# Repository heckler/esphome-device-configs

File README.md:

# ESPHome Device Configs

CAH, 2019-03-26 Configuration definitions for local ESPHome devices.

For information on removing secrets from the repository, see this link: <https://github.com/heckler/home-assistant-config/blob/master/secrets_cleanup.md>

## Device-specific configurations

- [ESP32 Camera modules](docs/esp32cam.md)
- [Flashing Sonoff Basic devices with ESPHome](docs/flashing_sonoff_basic.md)
- [Flashing Sonoff Basic R4 (Magic Switch) devices with ESPHome](docs/flashing_sonoff_basic_r4_magic.md)
- [Flashing Sonoff B1 LED bulbs with ESPHome](docs/flashing_sonoff_b1.md)
- [Configuration instructions for the WLED modules](docs/wled_modules.md)

------------------------------------------------------------------------------------------------

## Initial configuration

### Environment setup

- Getting started guide: [ESPHome Getting Started](https://esphome.io/guides/getting_started_command_line.html)
- WSL: ESPHome should already be configured via the wsl_provision bootstrap script

### DevContainers on VSCode

1. Install the VS Code DevContainers extension.
2. Open this folder in VS Code and run: `Dev Containers: Reopen in Container`.
3. Wait for the initial container build to complete. The container installs `esphome==2026.9.1` automatically.
4. Verify the install inside the container:

### DevContainers commandline on the shell

1. Install the DevContainers CLI: `npm install -g @devcontainers/cli`
2. Build and start the container: `devcontainer up --workspace-folder .`
3. Open a shell inside it: `devcontainer exec --workspace-folder . bash`

### Basic operation

```bash
esphome version
```

Start the dashboard from this repository root:

```bash
esphome dashboard .
```

Notes for USB serial flashing from DevContainer:

1. The DevContainer config binds `/dev` and uses `--privileged`, so serial devices (for example `/dev/ttyUSB0`) are available in the container.
2. Ensure your host user has serial permissions (typically membership in the `dialout` group on Linux).
3. Replug USB devices after opening the container if a serial device is not visible.

To update ESPHome:

```bash
pip3 install --upgrade esphome
pip3 install --upgrade virtualenv
```

To install a specific version:

```bash
pip3 uninstall esphome
pip3 install -Iv esphome==2026.6.2
```

The pip commands above are for local (non-DevContainer) installations.

### Updating ESPHome in the DevContainer

When a new ESPHome release is available, update the pinned version in the DevContainer config.

1. Edit the pinned version in `.devcontainer/devcontainer.json` by changing `postCreateCommand` from `esphome==...` to the new release.
2. In VS Code, run `Dev Containers: Rebuild Container`.
3. Confirm the new version:

```bash
esphome version
```

4. Run a quick config validation from the repository root:

```bash
esphome config balcony_sensors.yaml
```

### Creating a new device config (using the wizard)

`esphome hello-world.yaml wizard`

### Building and deploying

`esphome hello-world.yaml run`

### ESPHome dashboard

There is a simple dashboard webserver in ESPHome.  From the folder where the device configs are stored, execute the following command:

`esphome . dashboard`

Then, navigate to the following address: [http://localhost:6052/](http://localhost:6052/)

### Changing the name of a device via OTA

<https://esphome.io/components/esphome.html#changing-esphome-node-name>

1. Change the name of the device on the yaml
2. Use the `use_address` WiFi option to point to the old mDNS name
3. Upload the config, will rename the device, using the old name for OTA
4. Remove `use_address` and upload again (to confirm it finds the new name)

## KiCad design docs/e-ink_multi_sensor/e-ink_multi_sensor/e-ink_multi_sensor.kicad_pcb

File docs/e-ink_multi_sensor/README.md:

# Multi-sensor board with e-ink display

CAH 2026-09-19

## Overview

This is an ESP32-based device with an e-ink display (WeAct 4.2" 3-color) and a number of sensors.  It will read indoor and outdoor temperatures as well as CO2, barometric pressure and relative humidity. The main components are:

- ESP32: YD-ESP32-S3 / ESP32-S3-WROOM-1 Dev N16R8 (44-pin)
- WeAct 4.2" 400x300, 3-color e-ink display (white, black and red)
- BME280 sensor (Barometric pressure, temperature and relative humidity - to be placed outdoors)
- SCD41 (CO2, temperature and relative humidity - to be placed indoors)
- HC-SR501 PIR sensor (for updating the e-ink panel only when there's recent movement)
- WS2812b status LED (1-5 LEDs on a strip, to be defined)
- 2 capacitive switches for input

## Supplier links and price (2026)

| Device     |  Price | Link                                                |
| ---------- | -----: | --------------------------------------------------- |
| ESP32-S3   |  $5.47 | <https://aliexpress.com/item/1005009045226863.html> |
| WeAct 4.2" | $12.44 | <https://aliexpress.com/item/1005008461198386.html> |
| BME280     |  $7.74 | <https://aliexpress.com/item/1005010471387051.html> |
| SCD41      | $12.81 | <https://aliexpress.com/item/1005009392057489.html> |
| HC-SR501   |  $1.29 | <https://aliexpress.com/item/1005006438490597.html> |

## GPIO allocation

|   GPIO | Function       | Device             | Notes                    |
| -----: | -------------- | ------------------ | ------------------------ |
|  GPIO4 | I2C SDA        | BME280 + SCD41     | Good general-purpose pin |
|  GPIO5 | I2C SCL        | BME280 + SCD41     | Good general-purpose pin |
|  GPIO6 | SPI CLK / SCL  | WeAct 4.2" e-paper | E-paper SPI              |
|  GPIO7 | SPI MOSI / SDA | WeAct 4.2" e-paper | E-paper SPI              |
|  GPIO8 | CS             | WeAct 4.2" e-paper | Chip select              |
|  GPIO9 | DC             | WeAct 4.2" e-paper | Data/command             |
| GPIO10 | RST            | WeAct 4.2" e-paper | Display reset            |
| GPIO11 | BUSY           | WeAct 4.2" e-paper | Display busy input       |
| GPIO12 | PIR OUT        | HC-SR501           | Digital input            |
| GPIO13 | DATA           | WS2812B            | Drives 1-5 LEDs          |
| GPIO14 | Switch 1       | Pushbutton/switch  | Digital input            |
| GPIO15 | Switch 2       | Pushbutton/switch  | Digital input            |
| GPIO16 | -              | Spare              | Keep available           |
| GPIO17 | -              | Spare              | Keep available           |
| GPIO18 | -              | Spare              | Keep available           |
| GPIO21 | -              | Spare              | Keep available           |

## Reserved GPIOs

|           GPIO | Reason                                                 |
| -------------: | ------------------------------------------------------ |
| -        GPIO0 | Boot/strapping                                       - |
|          GPIO3 | Strapping                                              |
| -    GPIO19/20 | Native USB D-/D+                                       |
|   GPIO35/36/37 | N16R8 octal PSRAM                                      |
|      GPIO43/44 | USB-UART / UART0                                       |
|         GPIO45 | Strapping                                              |
|         GPIO46 | Strapping                                              |
|         GPIO48 | On-board RGB LED / special-purpose pin                 |
|      GPIO39-42 | JTAG pins; usable, but better retained for debugging   |

## ESPHome configuration

### ESP32 S3 board

```yaml
esp32:
  board: esp32-s3-devkitc-1
  framework:
    type: esp-idf
psram:
  mode: octal
  speed: 80MHz
```

### WeAct 4.2" 3-color e-ink panel

```yaml
spi:
  clk_pin: GPIO6
  mosi_pin: GPIO7

display:
  - platform: epaper_spi
    model: WeAct-4.2in-3c
    cs_pin: GPIO8
    dc_pin: GPIO9
    reset_pin: GPIO10
    busy_pin: GPIO11
```

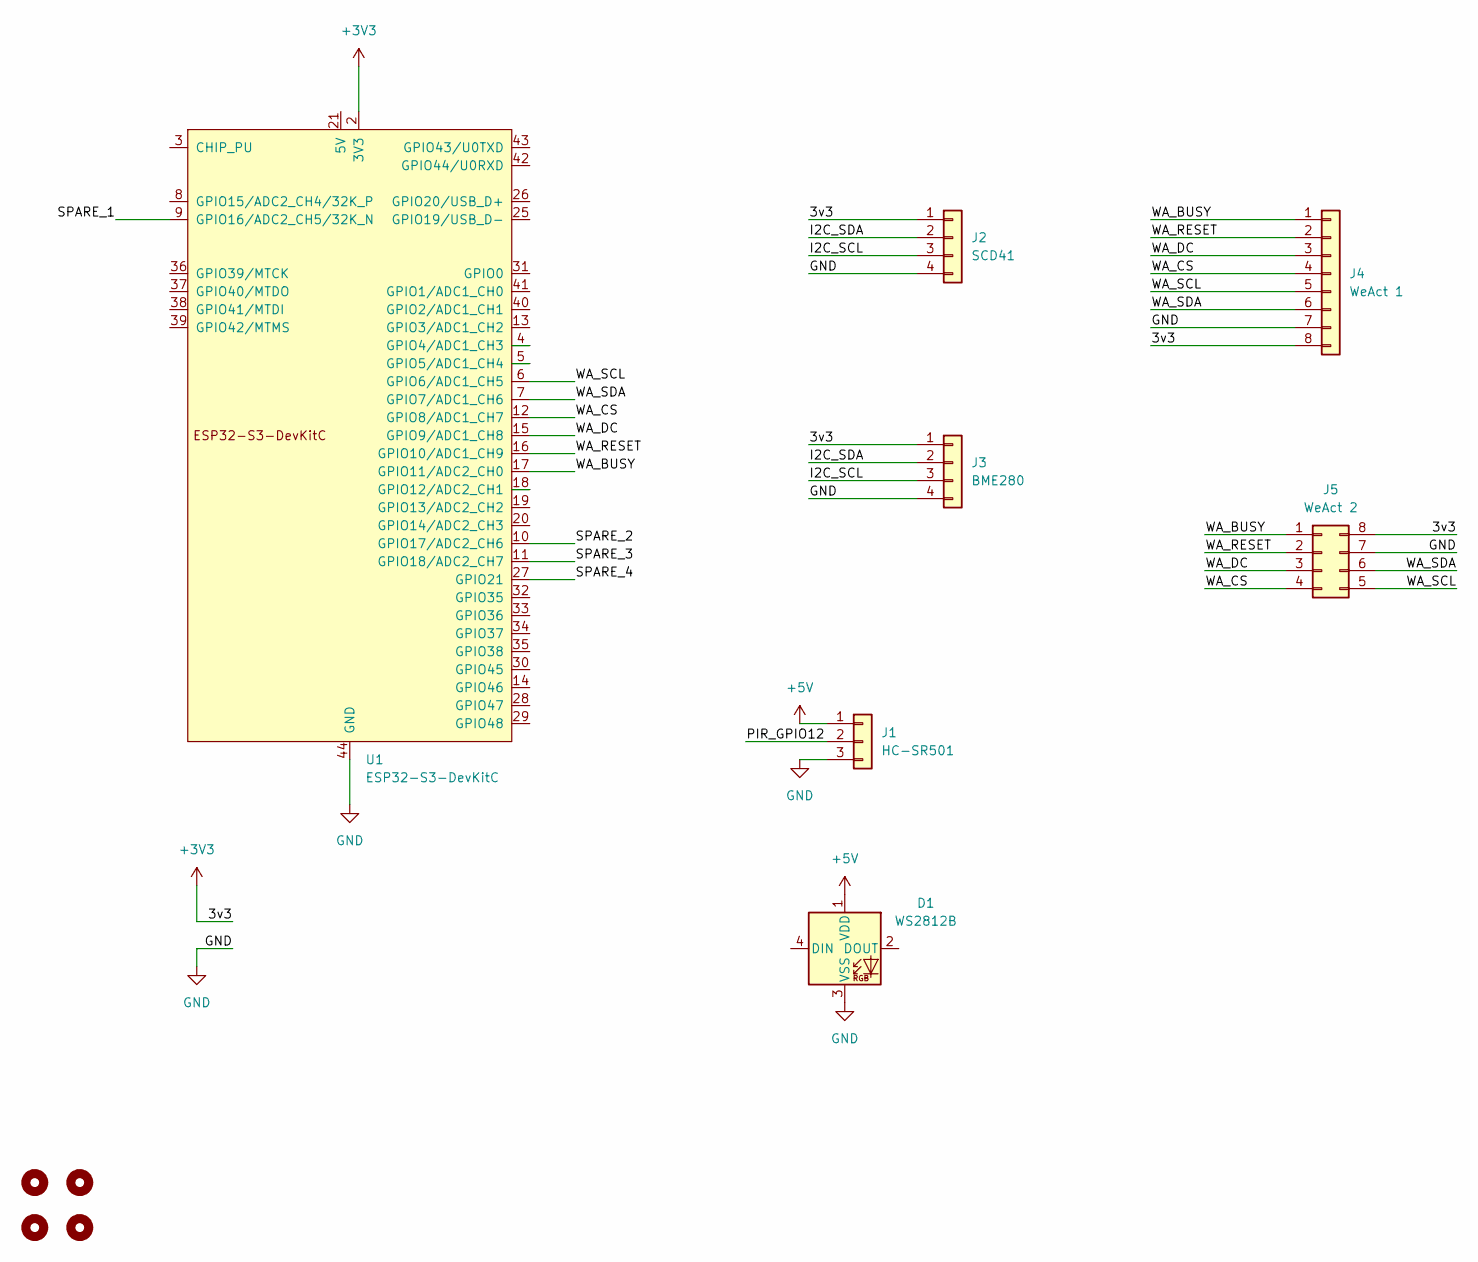
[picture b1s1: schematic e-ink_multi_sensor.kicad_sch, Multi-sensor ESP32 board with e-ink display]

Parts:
D1: WS2812B; LED_WS2812B_PLCC4_5.0x5.0mm_P3.2mm
H1, H2, H3, H4: MountingHole; MountingHole_3mm_Pad
J1: HC-SR501; JST_EH_B3B-EH-A_1x03_P2.50mm_Vertical
J2: SCD41; NS-Tech_Grove_1x04_P2mm_Vertical
J3: BME280; NS-Tech_Grove_1x04_P2mm_Vertical
J4: WeAct 1; JST_PH_B8B-PH-K_1x08_P2.00mm_Vertical
J5: WeAct 2; Hirose_DF11-8DP-2DSA_2x04_P2.00mm_Vertical
U1: ESP32-S3-DevKitC

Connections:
+3V3: J2.1, J3.1, J4.8, J5.8, U1.1 (3V3), U1.2 (3V3)
+5V: D1.1 (VDD), J1.1
/I2C_SCL: J2.3, J3.3
/I2C_SDA: J2.2, J3.2
/PIR_GPIO12: J1.2
/SPARE_1: U1.9 (GPIO16/ADC2_CH5/32K_N)
/SPARE_2: U1.10 (GPIO17/ADC2_CH6)
/SPARE_3: U1.11 (GPIO18/ADC2_CH7)
/SPARE_4: U1.27 (GPIO21)
/WA_BUSY: J4.1, J5.1, U1.17 (GPIO11/ADC2_CH0)
/WA_CS: J4.4, J5.4, U1.12 (GPIO8/ADC1_CH7)
/WA_DC: J4.3, J5.3, U1.15 (GPIO9/ADC1_CH8)
/WA_RESET: J4.2, J5.2, U1.16 (GPIO10/ADC1_CH9)
/WA_SCL: J4.5, J5.5, U1.6 (GPIO6/ADC1_CH5)
/WA_SDA: J4.6, J5.6, U1.7 (GPIO7/ADC1_CH6)
GND: D1.3 (VSS), J1.3, J2.4, J3.4, J4.7, J5.7, U1.22 (GND), U1.23 (GND), U1.24 (GND), U1.44 (GND)

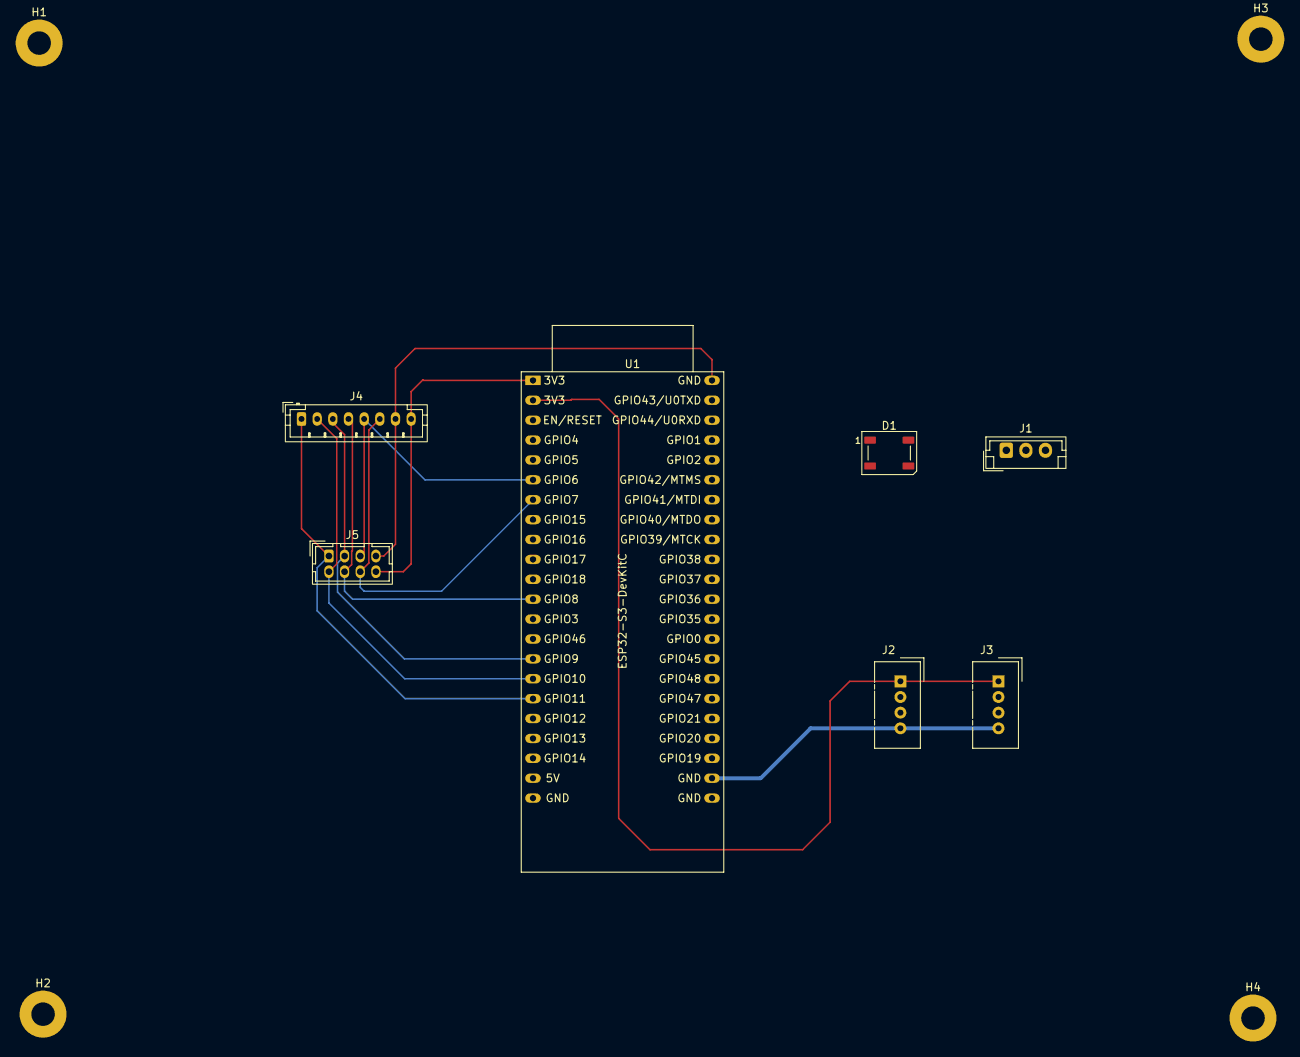
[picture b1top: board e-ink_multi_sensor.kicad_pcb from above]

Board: 2 copper layers, 11 parts (0 on the bottom side), 11 nets.

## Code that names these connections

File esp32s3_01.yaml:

# -----------------------------------------------------------------------------
# ESPHome config file for the ESP32-S3 module 01
# CAH 2026-10-13
#
#
# -----------------------------------------------------------------------------

substitutions:
  node_hostname: esp32s3_01
  node_name: "ESP32-S3 01"

packages:
  device_base: !include common/device_base.yaml
  platform: !include common/esp32s3.yaml


spi:
  clk_pin: GPIO6
  mosi_pin: GPIO7

http_request:
  verify_ssl: false
  timeout: 15s

image:
  - platform: online_image
    id: remote_image
    url: http://homeassistant.local:8123/local/epaper/screen.png
    format: PNG
    type: RGB
    resize: 400x300
    on_download_finished:
      - component.update: epaper

display:
  - platform: epaper_spi
    id: epaper
    model: WeAct-4.2in-3c
    cs_pin: GPIO8
    dc_pin: GPIO9
    reset_pin: GPIO10
    busy_pin: GPIO11
    update_interval: never
    lambda: |-
      it.fill(Color::WHITE);
      it.image(0, 0, id(remote_image));

text:
  - platform: template
    name: "E-Paper Image URL"
    id: image_url
    mode: text
    optimistic: true
    min_length: 1
    max_length: 255
    set_action:
      - online_image.set_url:
          id: remote_image
          url: !lambda 'return x;'

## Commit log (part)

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2019-03-27 initial device configs
2019-10-27 Added a template for the secrets file
2019-10-27 Additional folders in .gitignore
2019-10-28 got the two ESP32Cam modules working with ESPHome
2019-10-29 added info about the esphome dashboard
2019-10-30 deleted test.yaml, an old nodemcu test config
2019-10-30 added a version info sensor and a reset switch to all three device configs
2019-10-30 added an uptime sensor to both espcam configs
2019-10-30 updated sensor names; wifi mode set to minimal power saving
2019-11-01 debug-level logs and wifi status sensor
2019-11-01 trying a different wifi network; renamed wifi signal sensor
2019-11-02 Added first version of the new, BME280-based, balcony sensors module
2019-11-02 Enabled multiple wifi networks and ap mode with captive portal
2019-11-03 confirmed pin numbers
2019-11-03 Quick test to validate the PIR motion sensors are working
2019-11-04 Got the PIR and the display working
2019-11-04 Added a simple uptime test config, to determine why I was having stability issues with the NodeMCUs
2019-11-04 Switched power_save_mode from light to none on all devices, to solve stability issues
2019-11-05 Clear the display on boot; comment out BME280 (not connected yet); rename API endpoints
2019-11-07 Correct settings for BMP280 : now it is working!
2019-11-07 Remove wifi signal sensor; fix the name of the uptime sensor
2019-11-07 Display layout completed (mock values for the time being)
2019-11-09 started a schematic in fritzing
2019-11-09 starting the proto pcb layout
2019-11-09 continuing the pcb layout
2019-11-10 Added note about uploading via esptool.py with lower baud rate
2019-11-10 Trying adding two DHT-22 sensors, not sucessful - got into a boot loop, entries left commented out
2019-11-10 adding documentation stubs
2019-11-11 got the config working with two DHT-22 sensors
2019-11-12 showing actual sensor values in the OLED display
2019-11-12 showing sensor value trend indicators in the display
2019-11-13 note a couple minor bugs to report to esphome
2019-11-13 applying filtering over 5 values for the sensor data
2020-05-12 note on existing backup
2020-06-09 renamed layout file
2020-06-09 deleted unused vision file
2020-06-09 added schematic export image (still incomplete)
2020-06-09 new layout option
2020-07-12 added RJ45 breakout
2020-07-19 Added info on flashing sonoff devices with ESPHome
2020-07-19 Device profile for the fireplace light module
2020-09-16 fireplace_light fw uploaded to sonoff, working fine
2020-11-26 Note on secret cleanup
2020-11-26 set .pdn file to binary
2020-11-26 note on updating esphome
2020-11-26 updated layout for the new balcony sensors module
2020-11-27 CRLF to LF conversion
2020-12-01 added explicit config for frame rates and test pattern
2020-12-01 doc refactoring
2020-12-01 custom fireplace icon for the relay switch
2020-12-01 updated camera settings
2021-01-24 added a note about installing a specific version of ESPHome
2021-02-16 Added uptime to the fireplace light
2021-04-04 First version of the freezer sensor/alarm module (still without an actual alarm)
2021-04-04 fix case in sensor name
2021-04-06 Added a buzzer alarm when the temp climbs above -10oC
2021-04-07 goofing around: added pre-defined songs for invoking via API
2021-04-25 Added a configuration for a fridge dual temperature sensor and alarm
2021-04-29 remove startup beep (annoying on restart due to HA being out for a walk)
2021-04-29 tweak alarm setpoint to avoid false positives when defrosting
2021-10-10 Added firmware YAML file for the balcony irrigation pump (SONOFF)
2022-04-13 Starting to add documentation for flashing a Sonoff B1
2022-04-17 Still preparing to flash the Sonoff B1
2022-06-13 Added a reset switch to the API
2022-06-13 Added different serial port instructions for Linux and Windows
2022-06-13 first pass adding documentation for the wake-up lights
2022-09-19 remove pinned arduino version
2022-09-19 simple script to watch logs over the network
2022-10-11 added version info to both lights
2022-10-11 standardize on version reporting
2022-10-11 add light efects
2022-10-12 major refactoring leveraging substitutions and packages to reduce duplication
2022-10-12 use shorter hotspot AP SSID names
2022-10-20 document issue with Sonoff Basic and ESPHome version 2022.9.4
2022-10-20 added a substitution to set the icon of the switch on sonoff basic devices
2022-10-21 fix a mistake in the sonoff B1 package definition
2022-10-21 fix a hardcoded mistake in the esp32cam package
2022-11-24 added a workarround to issue with sonoff B1 runing on purple on reboot
2023-12-15 starting the docs for WLED modules
2024-04-17 Update README.md
    Fixed markup
2024-04-21 added notes on the WLED modules
2025-04-17 Re-assigning former fridge-sensors to dinning-room-sensors
2025-04-26 Fixed typo on dining_room_sensors
2025-04-26 Adding flashing instructions for Sonoff Basic R4 Magic Switch
2025-04-26 Adding the YAML configs for the Sonoff Basic R4 devices (with BLE disabled)
2025-12-29 Added info on reflashing the GLEDOPTO modules
2026-02-19 Added wakeup_light_03c, repurposing 01r
2026-06-26 Added a DevContainer profile
2026-06-26 updates required by ESPHome v2026.x.x
